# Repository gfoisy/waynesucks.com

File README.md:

# waynesucks.com

This repo is for sharing files with wayne

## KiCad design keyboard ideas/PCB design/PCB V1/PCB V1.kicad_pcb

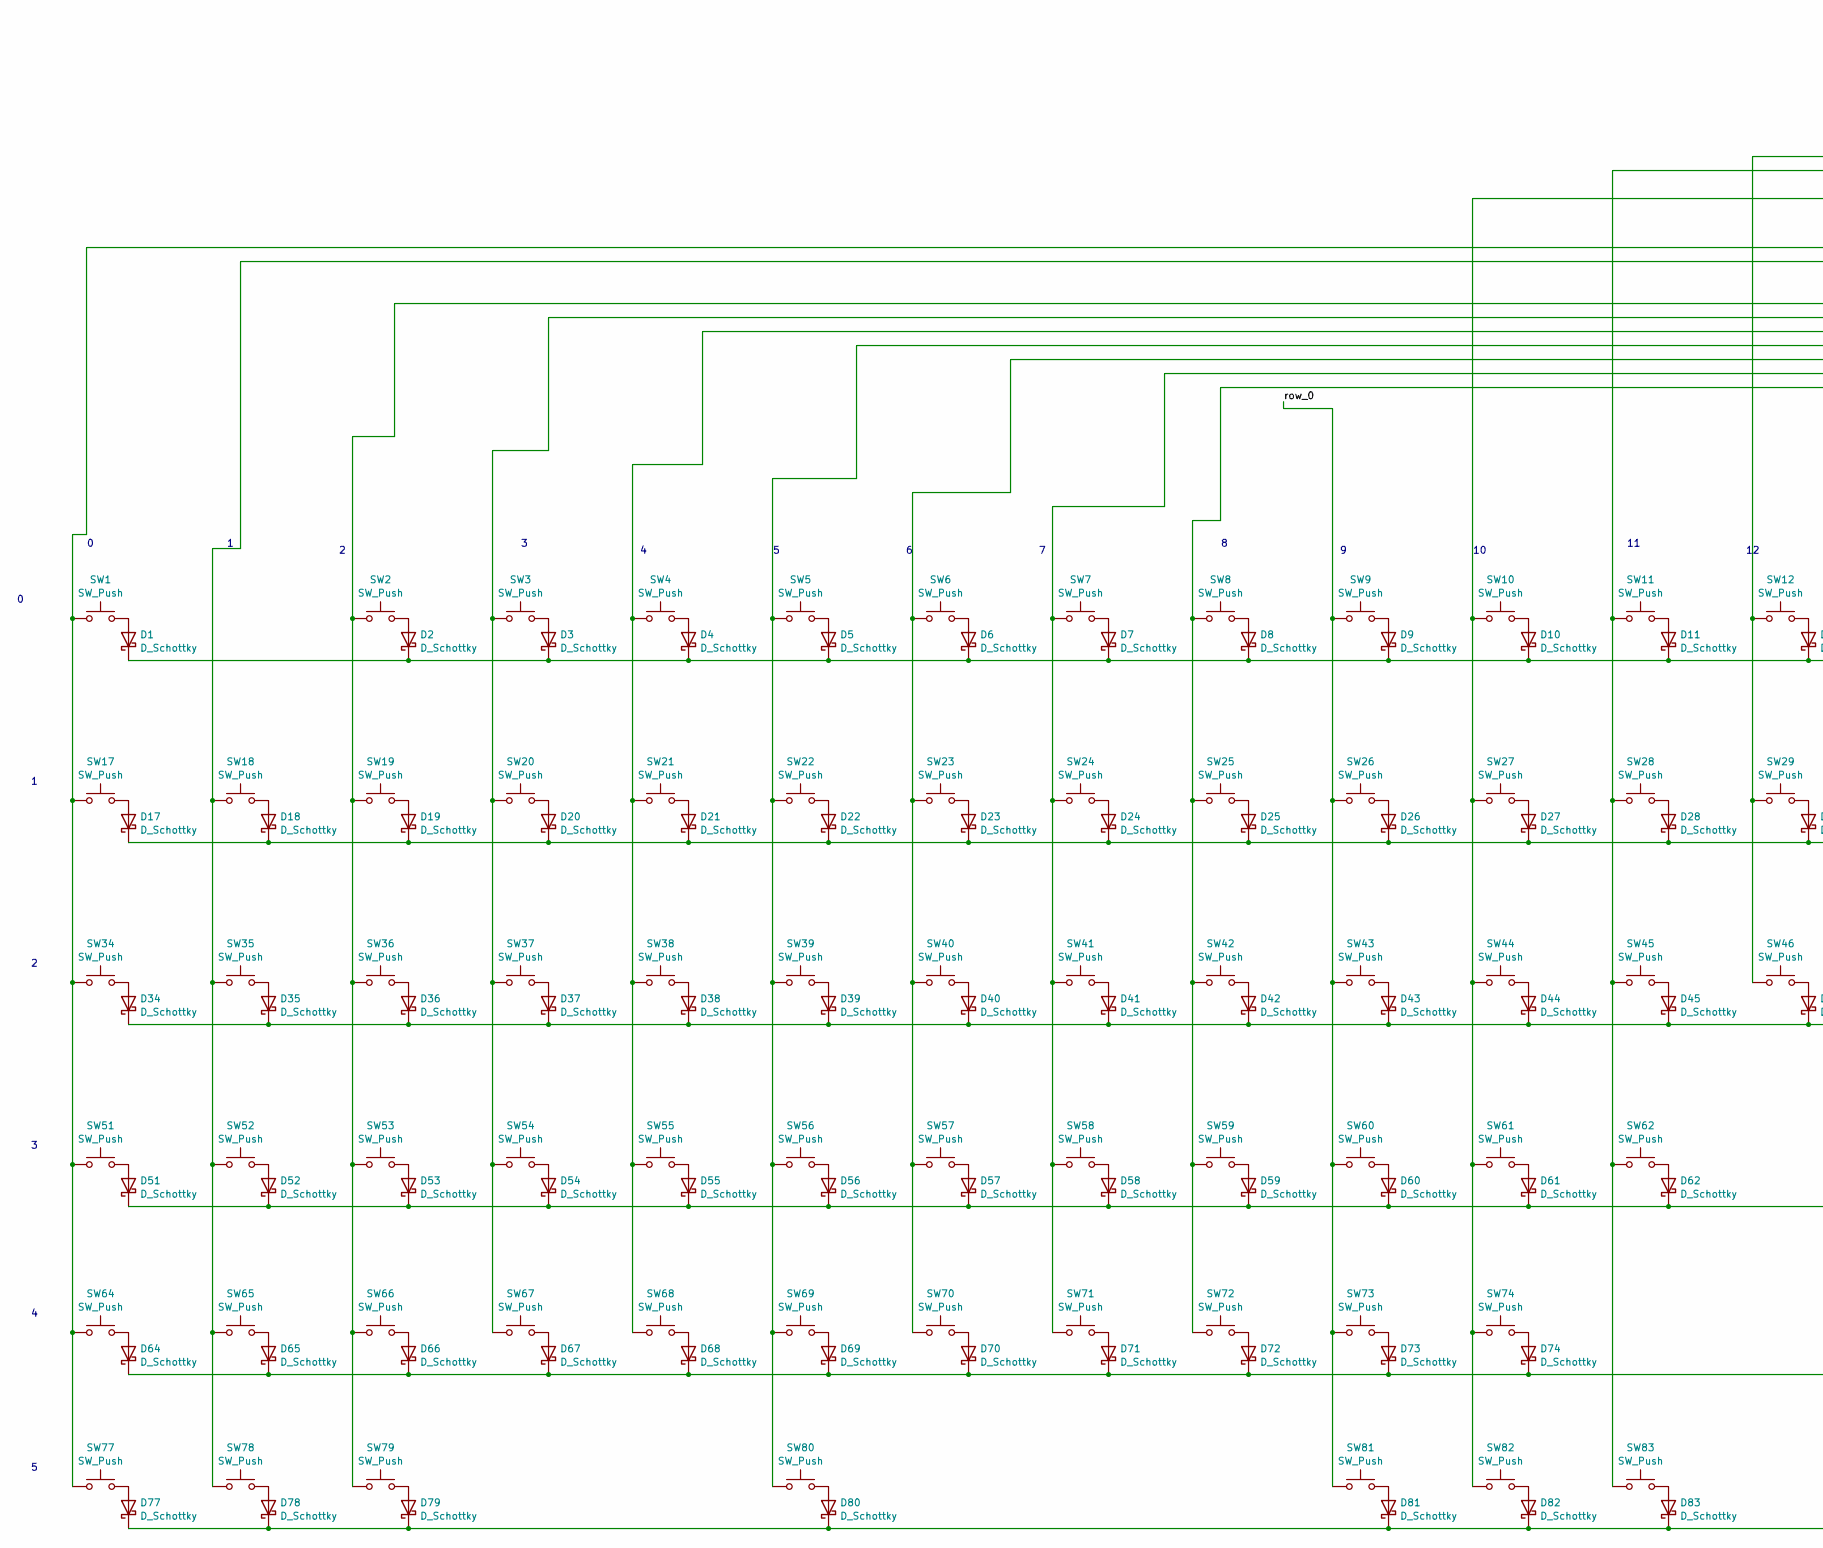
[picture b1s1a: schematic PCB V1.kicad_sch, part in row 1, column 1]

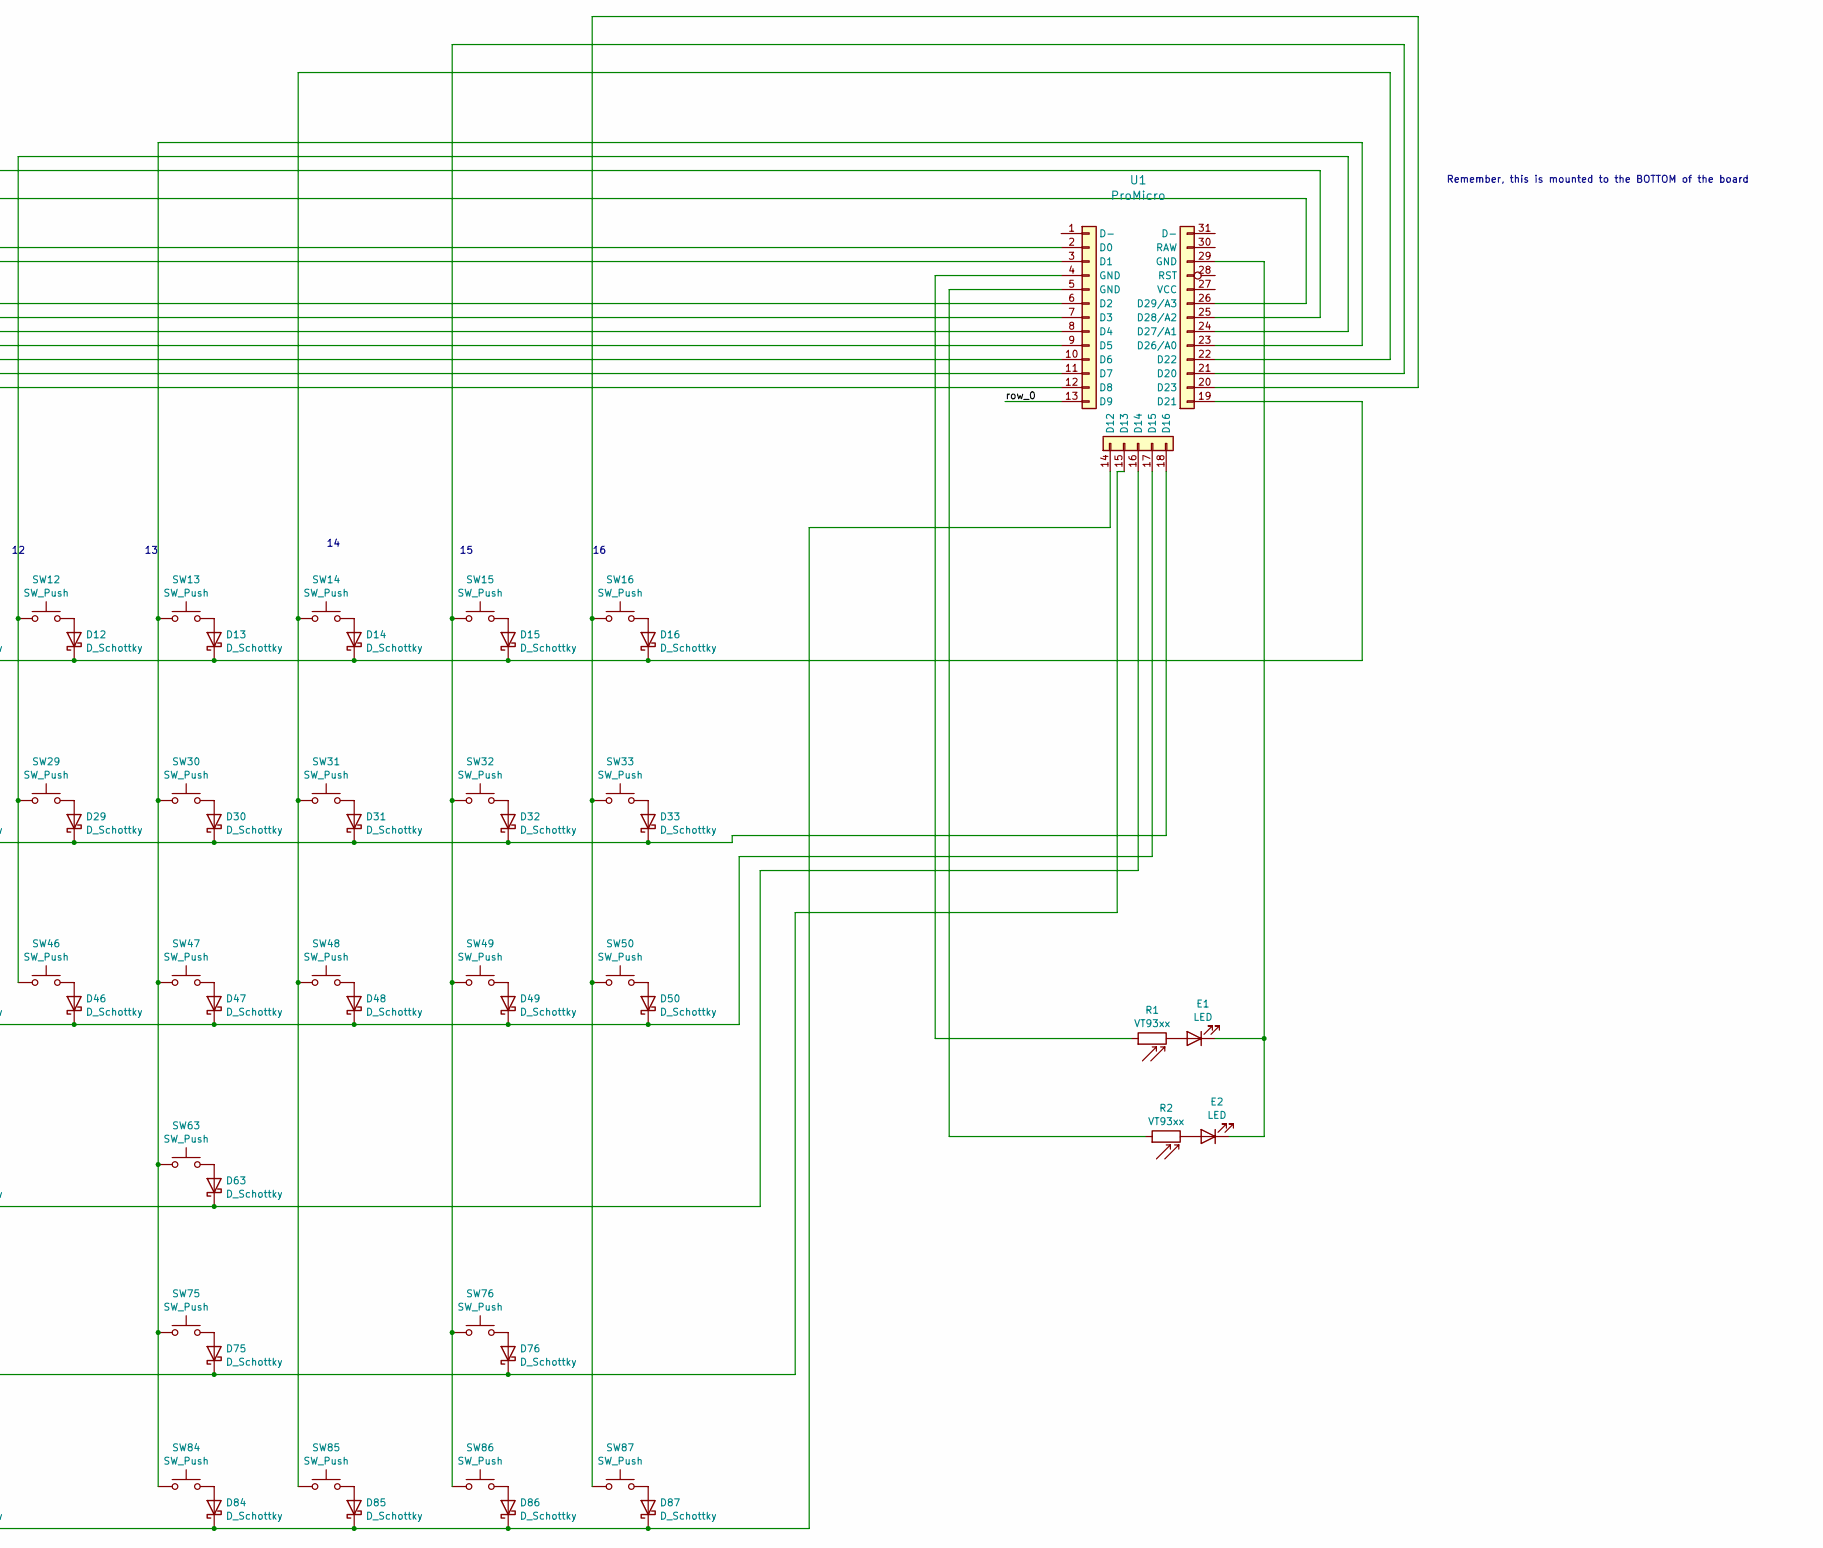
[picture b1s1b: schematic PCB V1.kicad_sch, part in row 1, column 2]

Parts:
D1, D2, D3, D4, D5, D6, D7, D8, D9, D10, D11, D12, D13, D14, D15, D16, D17, D18, D19, D20, D21, D22, D23, D24, D25, D26, D27, D28, D29, D30, D31, D32, D33, D34, D35, D36, D37, D38, D39, D40, D41, D42, D43, D44, D45, D46, D47, D48, D49, D50, D51, D52, D53, D54, D55, D56, D57, D58, D59, D60, D61, D62, D63, D64, D65, D66, D67, D68, D69, D70, D71, D72, D73, D74, D75, D76, D77, D78, D79, D80, D81, D82, D83, D84, D85, D86, D87: D_Schottky; D_SOD-123
E1, E2: LED; LED_D3.0mm_Horizontal_O1.27mm_Z2.0mm
R1, R2: VT93xx; R_LDR_4.9x4.2mm_P2.54mm_Vertical
SW1, SW2, SW3, SW4, SW5, SW6, SW7, SW8, SW9, SW10, SW11, SW12, SW13, SW14, SW15, SW16, SW17, SW18, SW19, SW20, SW21, SW22, SW23, SW24, SW25, SW26, SW27, SW28, SW29, SW30, SW31, SW32, SW33, SW34, SW35, SW36, SW37, SW38, SW39, SW40, SW41, SW42, SW43, SW44, SW45, SW46, SW47, SW48, SW49, SW50, SW51, SW52, SW53, SW54, SW55, SW56, SW57, SW58, SW59, SW60, SW61, SW62, SW63, SW64, SW65, SW66, SW67, SW68, SW69, SW70, SW71, SW72, SW73, SW74, SW75, SW76, SW77, SW78, SW79, SW80, SW81, SW82, SW83, SW84, SW85, SW86, SW87: SW_Push; SW_Cherry_MX_PCB
U1: ProMicro; PinHeader_2x13+5_P2.54mm_Vertical_Elite-C

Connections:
/row_0: SW9.1, SW26.1, SW43.1, SW60.1, SW73.1, SW81.1, U1.13 (D9)
unnamed: D1.2 (A), SW1.2
unnamed: D1.1 (K), D2.1 (K), D3.1 (K), D4.1 (K), D5.1 (K), D6.1 (K), D7.1 (K), D8.1 (K), D9.1 (K), D10.1 (K), D11.1 (K), D12.1 (K), D13.1 (K), D14.1 (K), D15.1 (K), D16.1 (K), U1.19 (D21)
unnamed: D2.2 (A), SW2.2
unnamed: D3.2 (A), SW3.2
unnamed: D4.2 (A), SW4.2
unnamed: D5.2 (A), SW5.2
unnamed: D6.2 (A), SW6.2
unnamed: D7.2 (A), SW7.2
unnamed: D8.2 (A), SW8.2
unnamed: D9.2 (A), SW9.2
unnamed: D10.2 (A), SW10.2
unnamed: D11.2 (A), SW11.2
unnamed: D12.2 (A), SW12.2
unnamed: D13.2 (A), SW13.2
unnamed: D14.2 (A), SW14.2
unnamed: D15.2 (A), SW15.2
unnamed: D16.2 (A), SW16.2
unnamed: D17.2 (A), SW17.2
unnamed: D17.1 (K), D18.1 (K), D19.1 (K), D20.1 (K), D21.1 (K), D22.1 (K), D23.1 (K), D24.1 (K), D25.1 (K), D26.1 (K), D27.1 (K), D28.1 (K), D29.1 (K), D30.1 (K), D31.1 (K), D32.1 (K), D33.1 (K), U1.18 (D16)
unnamed: D18.2 (A), SW18.2
unnamed: D19.2 (A), SW19.2
unnamed: D20.2 (A), SW20.2
unnamed: D21.2 (A), SW21.2
unnamed: D22.2 (A), SW22.2
unnamed: D23.2 (A), SW23.2
unnamed: D24.2 (A), SW24.2
unnamed: D25.2 (A), SW25.2
unnamed: D26.2 (A), SW26.2
unnamed: D27.2 (A), SW27.2
unnamed: D28.2 (A), SW28.2
unnamed: D29.2 (A), SW29.2
unnamed: D30.2 (A), SW30.2
unnamed: D31.2 (A), SW31.2
unnamed: D32.2 (A), SW32.2
unnamed: D33.2 (A), SW33.2
unnamed: D34.2 (A), SW34.2
unnamed: D34.1 (K), D35.1 (K), D36.1 (K), D37.1 (K), D38.1 (K), D39.1 (K), D40.1 (K), D41.1 (K), D42.1 (K), D43.1 (K), D44.1 (K), D45.1 (K), D46.1 (K), D47.1 (K), D48.1 (K), D49.1 (K), D50.1 (K), U1.17 (D15)
unnamed: D35.2 (A), SW35.2
unnamed: D36.2 (A), SW36.2
unnamed: D37.2 (A), SW37.2
unnamed: D38.2 (A), SW38.2
unnamed: D39.2 (A), SW39.2
unnamed: D40.2 (A), SW40.2
unnamed: D41.2 (A), SW41.2
unnamed: D42.2 (A), SW42.2
unnamed: D43.2 (A), SW43.2
unnamed: D44.2 (A), SW44.2
unnamed: D45.2 (A), SW45.2
unnamed: D46.2 (A), SW46.2
unnamed: D47.2 (A), SW47.2
unnamed: D48.2 (A), SW48.2
unnamed: D49.2 (A), SW49.2
unnamed: D50.2 (A), SW50.2
unnamed: D51.2 (A), SW51.2
unnamed: D51.1 (K), D52.1 (K), D53.1 (K), D54.1 (K), D55.1 (K), D56.1 (K), D57.1 (K), D58.1 (K), D59.1 (K), D60.1 (K), D61.1 (K), D62.1 (K), D63.1 (K), U1.16 (D14)
unnamed: D52.2 (A), SW52.2
unnamed: D53.2 (A), SW53.2
unnamed: D54.2 (A), SW54.2
unnamed: D55.2 (A), SW55.2
unnamed: D56.2 (A), SW56.2
unnamed: D57.2 (A), SW57.2
unnamed: D58.2 (A), SW58.2
unnamed: D59.2 (A), SW59.2
unnamed: D60.2 (A), SW60.2
unnamed: D61.2 (A), SW61.2
unnamed: D62.2 (A), SW62.2
unnamed: D63.2 (A), SW63.2
unnamed: D64.2 (A), SW64.2
unnamed: D64.1 (K), D65.1 (K), D66.1 (K), D67.1 (K), D68.1 (K), D69.1 (K), D70.1 (K), D71.1 (K), D72.1 (K), D73.1 (K), D74.1 (K), D75.1 (K), D76.1 (K), U1.15 (D13)
unnamed: D65.2 (A), SW65.2
unnamed: D66.2 (A), SW66.2
unnamed: D67.2 (A), SW67.2
unnamed: D68.2 (A), SW68.2
unnamed: D69.2 (A), SW69.2
unnamed: D70.2 (A), SW70.2
unnamed: D71.2 (A), SW71.2
unnamed: D72.2 (A), SW72.2
unnamed: D73.2 (A), SW73.2
unnamed: D74.2 (A), SW74.2
unnamed: D75.2 (A), SW75.2
unnamed: D76.2 (A), SW76.2
unnamed: D77.2 (A), SW77.2
unnamed: D77.1 (K), D78.1 (K), D79.1 (K), D80.1 (K), D81.1 (K), D82.1 (K), D83.1 (K), D84.1 (K), D85.1 (K), D86.1 (K), D87.1 (K), U1.14 (D12)
unnamed: D78.2 (A), SW78.2
unnamed: D79.2 (A), SW79.2
unnamed: D80.2 (A), SW80.2
unnamed: D81.2 (A), SW81.2
unnamed: D82.2 (A), SW82.2
unnamed: D83.2 (A), SW83.2
unnamed: D84.2 (A), SW84.2
unnamed: D85.2 (A), SW85.2
unnamed: D86.2 (A), SW86.2
unnamed: D87.2 (A), SW87.2
unnamed: E1.2 (A), R1.2
unnamed: E1.1 (K), E2.1 (K), U1.29 (GND)
unnamed: E2.2 (A), R2.2
unnamed: R1.1, U1.4 (GND)
unnamed: R2.1, U1.5 (GND)
unnamed: SW1.1, SW17.1, SW34.1, SW51.1, SW64.1, SW77.1, U1.2 (D0)
unnamed: SW18.1, SW35.1, SW52.1, SW65.1, SW78.1, U1.3 (D1)
unnamed: SW2.1, SW19.1, SW36.1, SW53.1, SW66.1, SW79.1, U1.6 (D2)
unnamed: SW3.1, SW20.1, SW37.1, SW54.1, SW67.1, U1.7 (D3)
unnamed: SW4.1, SW21.1, SW38.1, SW55.1, SW68.1, U1.8 (D4)
unnamed: SW5.1, SW22.1, SW39.1, SW56.1, SW69.1, SW80.1, U1.9 (D5)
unnamed: SW6.1, SW23.1, SW40.1, SW57.1, SW70.1, U1.10 (D6)
unnamed: SW7.1, SW24.1, SW41.1, SW58.1, SW71.1, U1.11 (D7)
unnamed: SW8.1, SW25.1, SW42.1, SW59.1, SW72.1, U1.12 (D8)
unnamed: SW15.1, SW32.1, SW49.1, SW76.1, SW86.1, U1.21 (D20)
unnamed: SW14.1, SW31.1, SW48.1, SW85.1, U1.22 (D22)
unnamed: SW16.1, SW33.1, SW50.1, SW87.1, U1.20 (D23)
unnamed: SW13.1, SW30.1, SW47.1, SW63.1, SW75.1, SW84.1, U1.23 (D26/A0)
unnamed: SW12.1, SW29.1, SW46.1, U1.24 (D27/A1)
unnamed: SW11.1, SW28.1, SW45.1, SW62.1, SW83.1, U1.25 (D28/A2)
unnamed: SW10.1, SW27.1, SW44.1, SW61.1, SW74.1, SW82.1, U1.26 (D29/A3)

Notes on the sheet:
Remember, this is mounted to the BOTTOM of the board

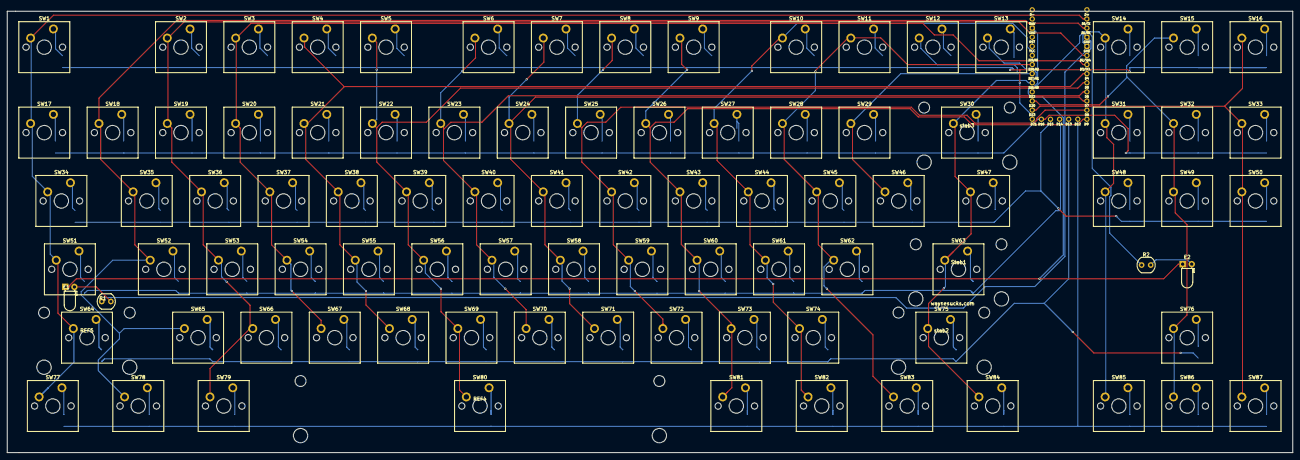
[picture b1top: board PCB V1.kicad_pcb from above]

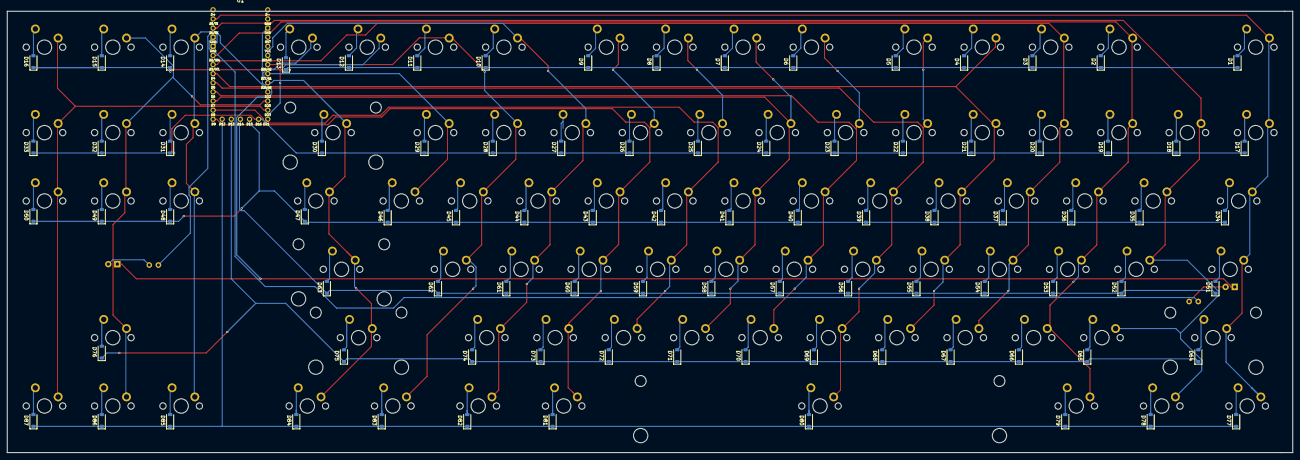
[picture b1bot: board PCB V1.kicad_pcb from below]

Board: 2 copper layers, 358.3 x 123.0 mm, 184 parts (88 on the bottom side), 115 nets.

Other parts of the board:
REF4: Stabilizer_Cherry_MX_6.25u
REF5: Stabilizer_Cherry_MX_2.00u
Stab1: Stabilizer_Cherry_MX_2.00u
stab2, stab3: Stabilizer_Cherry_MX_2.00u

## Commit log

2023-07-02 test commit
2023-07-05 asfd
    r
2023-07-05 updating the file for wayne
    sdfa
2023-07-17 keyboard roughed in
2023-07-18 some screws added
2023-07-21 ADDINGS SCREWS FOR MANUFACTURABILITY
2023-07-21 MORE UPODATED
2023-07-21 fixed teh thing
2023-07-22 I dont remember
2023-07-22 dummy feet and logo
    Added dummy feet. placed logo
